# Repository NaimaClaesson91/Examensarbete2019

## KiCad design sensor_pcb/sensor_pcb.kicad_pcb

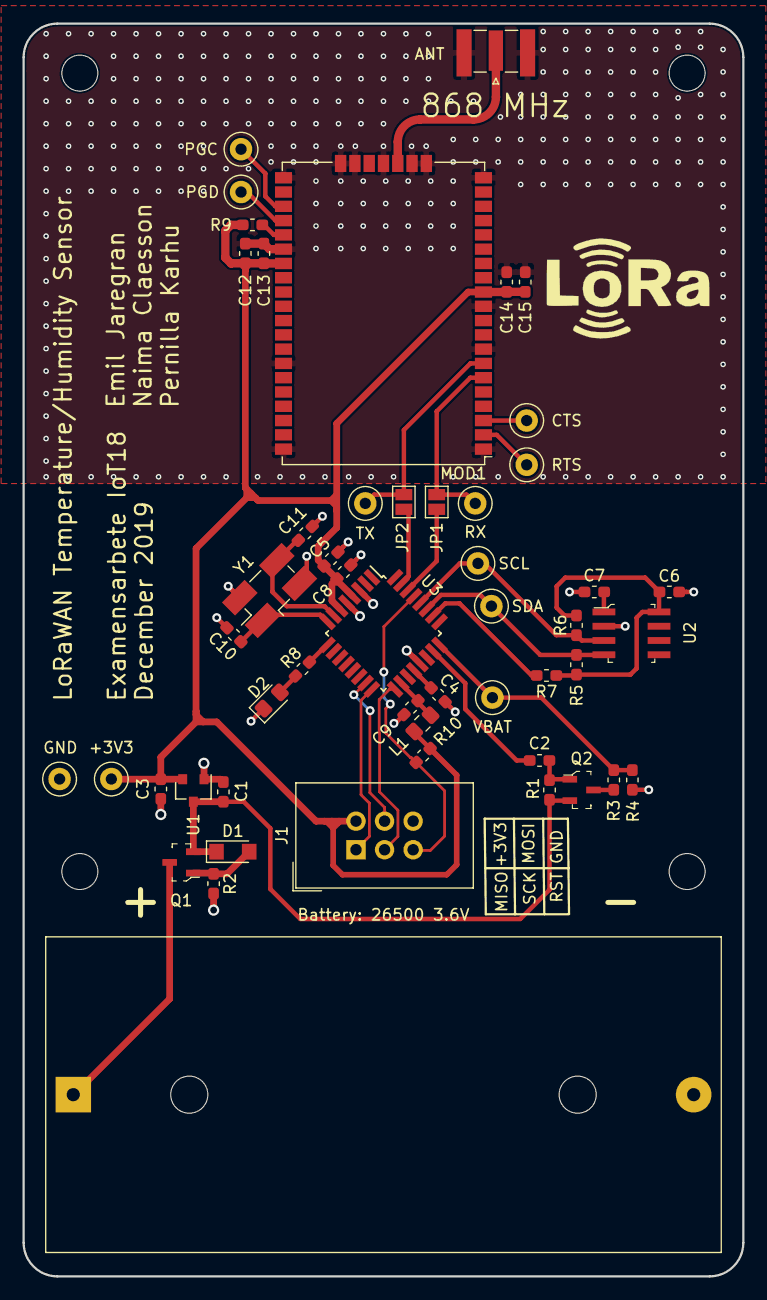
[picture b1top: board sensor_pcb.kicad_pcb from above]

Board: 2 copper layers, 64.0 x 111.4 mm, 53 parts (0 on the bottom side), 36 nets.

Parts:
+3V3: +3V3; TestPoint_Loop_D2.50mm_Drill1.0mm
ANT: SMA female; SMA_Samtec_SMA-J-P-X-ST-EM1_EdgeMount
Battery: 26500 3.6V: SAFT LS 26500; BatteryHolder_BHC-2
C1, C3: 1uF; C_0603_1608Metric_Pad1.05x0.95mm_HandSolder
C2, C4, C7, C8, C9, C13, C14: 100nF; C_0603_1608Metric_Pad1.05x0.95mm_HandSolder
C5, C12, C15: 10uF; C_0603_1608Metric_Pad1.05x0.95mm_HandSolder
C6: 220nF; C_0603_1608Metric_Pad1.05x0.95mm_HandSolder
C10, C11: 18pF; C_0603_1608Metric_Pad1.05x0.95mm_HandSolder
CTS: UART_CTS; TestPoint_Loop_D2.50mm_Drill1.0mm
D1: BZD27C10P; DO219-AB
D2: LED; LED_0805_2012Metric_Pad1.15x1.40mm_HandSolder
GND: GND; TestPoint_Loop_D2.50mm_Drill1.0mm
J1: AVR-ISP-6; IDC-Header_2x03_P2.54mm_Vertical
J3, J4: Arc; 2.0 mm arc
JP1: RX; SolderJumper-2_P1.3mm_Open_Pad1.0x1.5mm
JP2: TX; SolderJumper-2_P1.3mm_Open_Pad1.0x1.5mm
L1: 10uH; L_0805_2012Metric_Pad1.15x1.40mm_HandSolder
MOD1: RN2483A-I_RM105; RN2483
PGC: PGC_INT; TestPoint_Loop_D2.50mm_Drill1.0mm
PGD: PGD_INT; TestPoint_Loop_D2.50mm_Drill1.0mm
Q1, Q2: AO3401A; SOT-23-3
R1, R3, R9, R10: 10k; R_0603_1608Metric_Pad1.05x0.95mm_HandSolder
R2: 100k; R_0603_1608Metric_Pad1.05x0.95mm_HandSolder
R4: 47k; R_0603_1608Metric_Pad1.05x0.95mm_HandSolder
R5, R6: 2.2k; R_0603_1608Metric_Pad1.05x0.95mm_HandSolder
R7: 220R; R_0603_1608Metric_Pad1.05x0.95mm_HandSolder
R8: 1k; R_0603_1608Metric_Pad1.05x0.95mm_HandSolder
RTS: UART_RTS; TestPoint_Loop_D2.50mm_Drill1.0mm
RX: RX; TestPoint_Loop_D2.50mm_Drill1.0mm
SCL: SCL; TestPoint_Loop_D2.50mm_Drill1.0mm
SDA: SDA; TestPoint_Loop_D2.50mm_Drill1.0mm
TX: TX; TestPoint_Loop_D2.50mm_Drill1.0mm
U1: MCP1700-3302E_SOT23; SOT-23
U2: HIH6131-021-001; Humidity_HIH61xx
U3: ATmega328P-AU; TQFP-32_7x7mm_P0.8mm
VBAT: VBAT; TestPoint_Loop_D2.50mm_Drill1.0mm
Y1: 8 MHz; Crystal_SMD_EuroQuartz_MJ-4Pin_5.0x3.2mm_HandSoldering

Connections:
+3.3VA: C9.1, L1.2, U3.18
+3V3: +3V3.1, C3.1, C5.1, C8.1, C12.1, C13.1, C14.1, C15.1, J1.2, L1.1, MOD1.12, MOD1.34, R9.2, R10.2, U1.2, U3.4, U3.6
+BATT: C1.1, D1.1, Q1.2, Q2.2, R1.2, U1.3
/BAT_MON_EN: C2.2, U3.23
/HIH6131_EN: R7.2, U3.26
/LED: R8.2, U3.9
/MISO: J1.1, U3.16
/MOSI: J1.4, U3.15
/RESET: J1.5, R10.1, U3.29
/SCK: J1.3, U3.17
/SCL: R6.1, SCL.1, U2.3, U3.28
/SDA: R5.1, SDA.1, U2.4, U3.27
/UART_RX: JP1.2, MOD1.6, RX.1
/UART_TX: JP2.2, MOD1.7, TX.1
/VBAT: R3.1, R4.2, U3.24, VBAT.1
GND: ANT.2, Battery: 26500 3.6V.2, C1.2, C3.2, C4.2, C5.2, C6.2, C7.2, C8.2, C9.2, C10.2, C11.2, C12.2, C13.2, C14.2, C15.2, D2.1, GND.1, J1.6, MOD1.1, MOD1.8, MOD1.11, MOD1.20, MOD1.21, MOD1.22, MOD1.24, MOD1.26, MOD1.27, MOD1.28, MOD1.33, MOD1.41, MOD1.47, R2.1, R4.1, U1.1, U2.2, U3.3, U3.5, U3.21, Y1.2, Y1.4
unnamed: Battery: 26500 3.6V.1, Q1.3
unnamed: C2.1, Q2.1, R1.1
unnamed: C4.1, U3.20
unnamed: C6.1, R5.2, R6.2, R7.1, U2.8
unnamed: C7.1, U2.1
unnamed: C10.1, U3.8, Y1.1
unnamed: C11.1, U3.7, Y1.3
unnamed: D1.2, Q1.1, R2.2
unnamed: D2.2, R8.1
unnamed: ANT.1, J4.2
unnamed: J3.1, MOD1.23
unnamed: J3.2, J4.1
unnamed: JP1.1, U3.30
unnamed: JP2.1, U3.31
unnamed: MOD1.2, RTS.1
unnamed: CTS.1, MOD1.3
unnamed: MOD1.30, PGC.1
unnamed: MOD1.31, PGD.1
unnamed: MOD1.32, R9.1
unnamed: Q2.3, R3.2

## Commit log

2019-11-26 testing
2019-11-27 Get version from RN2483 working
2019-11-27 Implemented sys commands (except gpio)
2019-11-27 Refactored for easier integration of more commands
2019-11-27 Some refactoring and added most of the radio commands
2019-11-27 Implemented LoRaWAN protocol commands
2019-11-28 Uploading GPS test code for Arduino UNO
2019-11-28 Added TinyGPS+ lib
2019-11-28 added gps schematic
2019-11-29 node-RED test
2019-11-29 test flow in nodeRED
2019-11-29 ttn to influxdb test
2019-11-29 changed key names in msg
2019-11-29 Activation By Personalization working now
2019-11-29 Added frequency plan config for EU863-870
2019-11-29 OTAA join now working
2019-12-02 ATmega328P wakeup controlled by LoRa modem working
2019-12-02 added DeviceId field for testing
2019-12-03 HIH6131 raw reading working
2019-12-03 Adding code for LCD and TTN Mapper project
2019-12-03 Adding LCD and GPS code together and testing
2019-12-03 Working on code for TTN Mapper
2019-12-05 Added LoRa Shield and had to change alot of pins
2019-12-05 Added ignorefile and LoRa Shiled code
2019-12-05 Added Sensor PCB
2019-12-07 Added sensor case
2019-12-09 test code for tempsensor
2019-12-09 test code for temp sensor
2019-12-09 adc battery test
2019-12-09 Added buttons with voltage divider
2019-12-09 Updated gitignore file
2019-12-09 Added buttons on Kicad
2019-12-10 Working on schematic for TTN Mapper
2019-12-10 Worked further on TTN mapper and fixed a bug in main file
2019-12-10 Updated with new keys to Lora Shield and TTN
2019-12-11 test code for lora device, ttn
2019-12-12 Fixed button debouncing and button count
2019-12-13 Cleanup of TTN Mapper schematic
2019-12-13 Added programming header to TTN Mapper
2019-12-13 Added footprints to TTN mapper
2019-12-13 Added perf board netlist
2019-12-13 sleep mode working
2019-12-15 Added tests for the sensor
2019-12-15 Updated .gitignore
2019-12-16 Changed resistor values in scanner circuit
2019-12-16 Added sensor case with round SMA connector
2019-12-16 added join attempts
2019-12-17 code for prototyp 2 working
2019-12-17 working flow
